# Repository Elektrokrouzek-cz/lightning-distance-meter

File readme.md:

# Lightning distance meter
This is the construction of lightning distance meter. It is based on NE555 timer 
and 4017 logical circuits. All components are in THT packages.

PCB is 2-layer and was designed using KiCad 8. Fabrication output for JLCPCB is in 
gerber folder.

## How it works
This meter measures distance between lightning and thunder by measuring the time.
Speed of sound is 343 m/s therefore it takes approx. 291ms to the sound to travel
100m (this is the period of NE555 timer). 
User pushes Start button when lightning occurs and then presses Stop button when 
hears the thunder. LED diodes show measured distance. Maximal measurable distance is 9.9km. 

**Happy soldering!**

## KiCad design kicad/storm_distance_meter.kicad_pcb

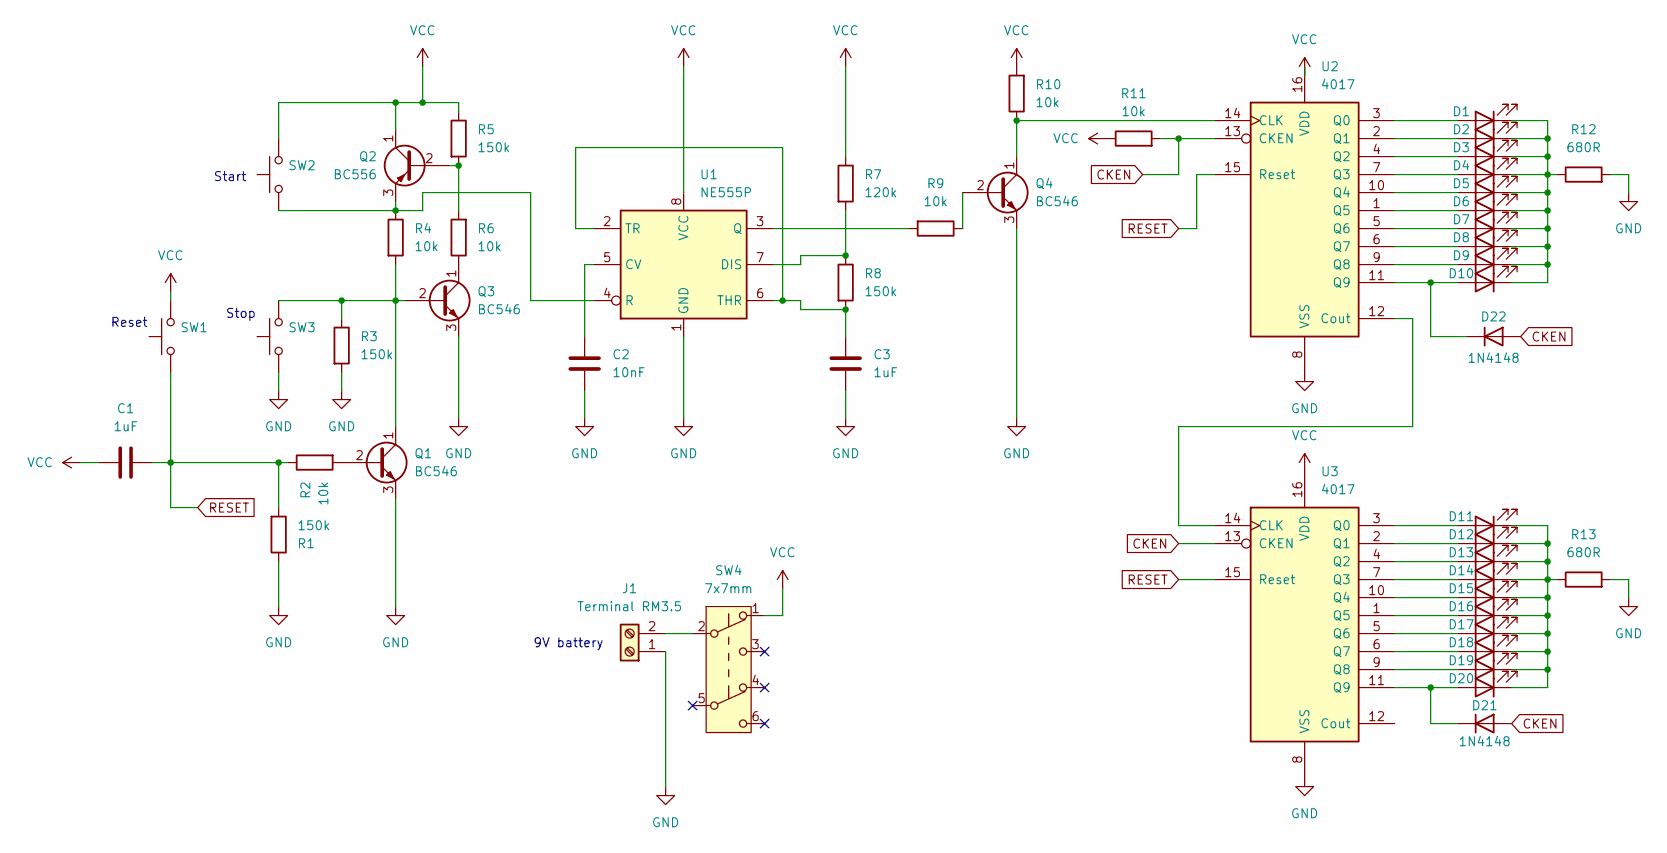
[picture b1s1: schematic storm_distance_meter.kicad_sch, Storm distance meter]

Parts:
C1, C3: 1uF; C_Disc_D5.0mm_W2.5mm_P5.00mm
C2: 10nF; C_Disc_D5.0mm_W2.5mm_P5.00mm
D1, D2, D3, D4, D5, D6, D7, D8, D9, D10: LED 3mm Y; LED_D3.0mm
D11, D12, D13, D14, D15, D16, D17, D18, D19, D20: LED 3mm G; LED_D3.0mm
D21, D22: 1N4148; D_DO-35_SOD27_P7.62mm_Horizontal
J1: Terminal RM3.5; TerminalBlock_4Ucon_1x02_P3.50mm_Horizontal
Q1, Q3, Q4: BC546; TO-92_Inline_Wide
Q2: BC556; TO-92_Inline_Wide
R1, R3, R5, R8: 150k; R_Axial_DIN0207_L6.3mm_D2.5mm_P7.62mm_Horizontal
R2, R4, R6, R9, R10, R11: 10k; R_Axial_DIN0207_L6.3mm_D2.5mm_P7.62mm_Horizontal
R7: 120k; R_Axial_DIN0207_L6.3mm_D2.5mm_P7.62mm_Horizontal
R12, R13: 680R; R_Axial_DIN0207_L6.3mm_D2.5mm_P7.62mm_Horizontal
SW1, SW2, SW3: 6mm; SW_PUSH_6mm_H9.5mm
SW4: 7x7mm; SW_DPDT_7x7_Turbo
U1: NE555P; DIP-8_W7.62mm
U2, U3: 4017; DIP-16_W7.62mm_LongPads

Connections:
CKEN: D21.2 (A), D22.2 (A), R11.2, U2.13 (CKEN), U3.13 (CKEN)
GND: C2.2, C3.2, J1.1, Q1.3 (E), Q3.3 (E), Q4.3 (E), R1.1, R3.2, R12.2, R13.2, SW3.1, U1.1 (GND), U2.8 (VSS), U3.8 (VSS)
unnamed: D1.2 (A), U2.3 (Q0)
unnamed: D1.1 (K), D2.1 (K), D3.1 (K), D4.1 (K), D5.1 (K), D6.1 (K), D7.1 (K), D8.1 (K), D9.1 (K), D10.1 (K), R12.1
unnamed: D2.2 (A), U2.2 (Q1)
unnamed: D3.2 (A), U2.4 (Q2)
unnamed: D4.2 (A), U2.7 (Q3)
unnamed: D5.2 (A), U2.10 (Q4)
unnamed: D6.2 (A), U2.1 (Q5)
unnamed: D7.2 (A), U2.5 (Q6)
unnamed: D8.2 (A), U2.6 (Q7)
unnamed: D9.2 (A), U2.9 (Q8)
unnamed: D10.2 (A), D22.1 (K), U2.11 (Q9)
unnamed: D11.2 (A), U3.3 (Q0)
unnamed: D11.1 (K), D12.1 (K), D13.1 (K), D14.1 (K), D15.1 (K), D16.1 (K), D17.1 (K), D18.1 (K), D19.1 (K), D20.1 (K), R13.1
unnamed: D12.2 (A), U3.2 (Q1)
unnamed: D13.2 (A), U3.4 (Q2)
unnamed: D14.2 (A), U3.7 (Q3)
unnamed: D15.2 (A), U3.10 (Q4)
unnamed: D16.2 (A), U3.1 (Q5)
unnamed: D17.2 (A), U3.5 (Q6)
unnamed: D18.2 (A), U3.6 (Q7)
unnamed: D19.2 (A), U3.9 (Q8)
unnamed: D20.2 (A), D21.1 (K), U3.11 (Q9)
unnamed: J1.2, SW4.2 (B)
unnamed: Q1.2 (B), R2.2
unnamed: Q1.1 (C), Q3.2 (B), R3.1, R4.2, SW3.2
unnamed: Q2.2 (B), R5.2, R6.2
unnamed: Q2.3 (E), R4.1, SW2.1, U1.4 (R)
unnamed: Q3.1 (C), R6.1
unnamed: Q4.2 (B), R9.1
unnamed: Q4.1 (C), R10.1, U2.14 (CLK)
unnamed: C2.1, U1.5 (CV)
unnamed: R7.2, R8.1, U1.7 (DIS)
unnamed: R9.2, U1.3 (Q)
unnamed: C3.1, R8.2, U1.2 (TR), U1.6 (THR)
unnamed: U2.12 (Cout), U3.14 (CLK)
RESET: C1.2, R1.2, R2.1, SW1.1, U2.15 (Reset), U3.15 (Reset)
VCC: C1.1, Q2.1 (C), R5.1, R7.1, R10.2, R11.1, SW1.2, SW2.2, SW4.1 (A), U1.8 (VCC), U2.16 (VDD), U3.16 (VDD)

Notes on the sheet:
Reset
9V battery
Stop
Start

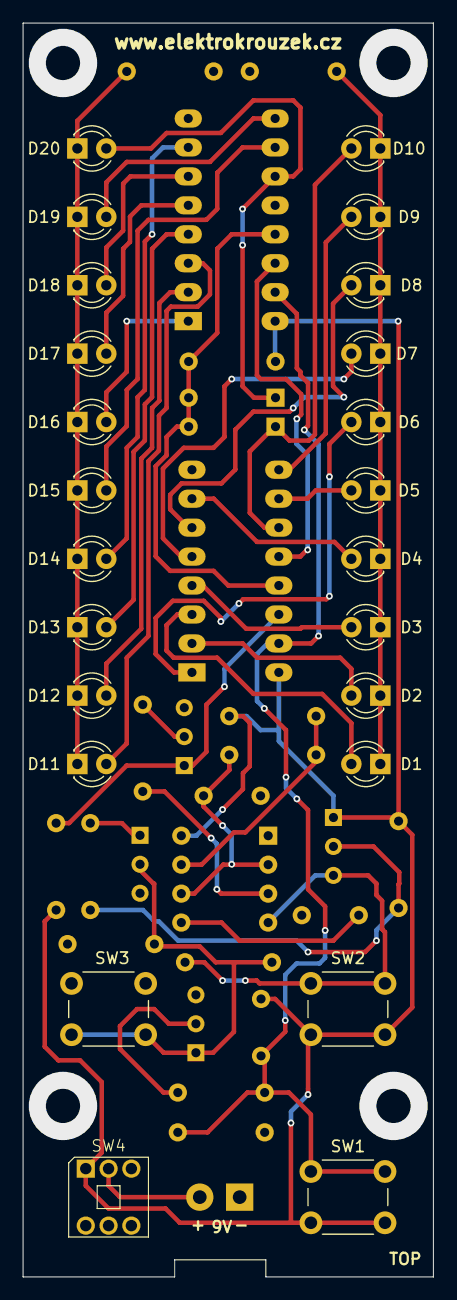
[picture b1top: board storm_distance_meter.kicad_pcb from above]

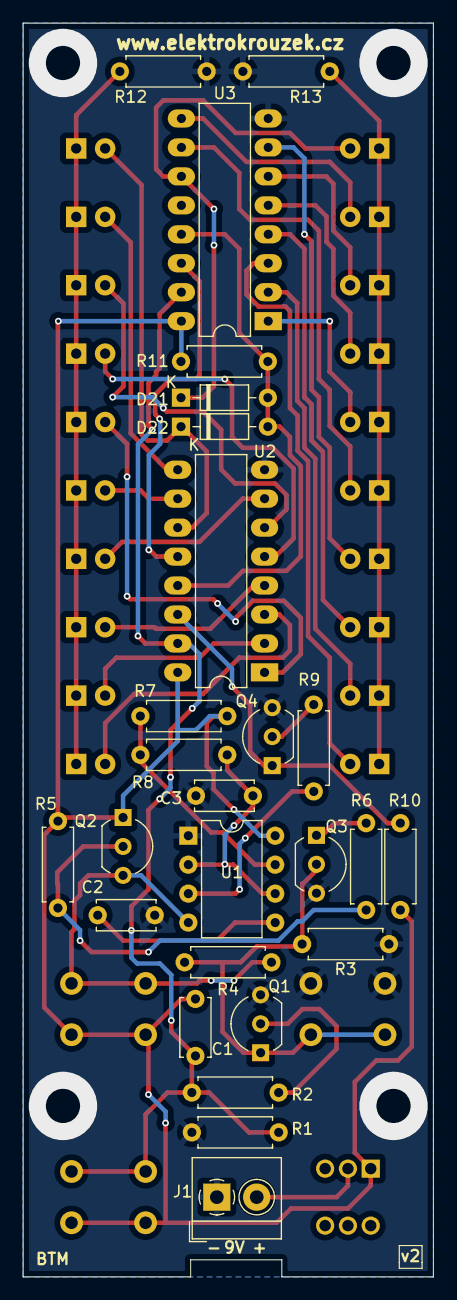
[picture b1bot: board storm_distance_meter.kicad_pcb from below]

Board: 2 copper layers, 36.0 x 110.0 mm, 50 parts (26 on the bottom side), 39 nets.

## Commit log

2025-01-21 PDF schematic added
2025-06-05 Updated PCB, manuals
2025-06-17 3D models
